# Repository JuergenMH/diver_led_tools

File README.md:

# diver_led_tools
This repository contains two projects or units.

The first one is a LED "Diver marker" and the second one is "Diver flasher".
Both devices are tools for scuba drivers.
It shares some ressources, this was the reason to put them into one repository.

## Folders
    2D drawings:            brainstorming folder with ideas how to create possible water proofed housings for the diver marker/flasher.
    documents:              different documents regarding both units.
    Firmware_diver_flasher: currently a copy of an older project which will be the base for the new software
    FIrmware_diver_marker:  ditto
    Pcb_Diver_Marker:       Eagle (7.6) PCB for this unit
    Pcb_Diver_Flasher:      KiCAD (8.0) PCB for this unit
    SKEDD-PIC-Cable:        KiCAD (8.0) schematic for the connection cable PICKIT <> PCB for program and debug purposes

## Current state (14.12.2024)
The folder structures and content are still under construction!

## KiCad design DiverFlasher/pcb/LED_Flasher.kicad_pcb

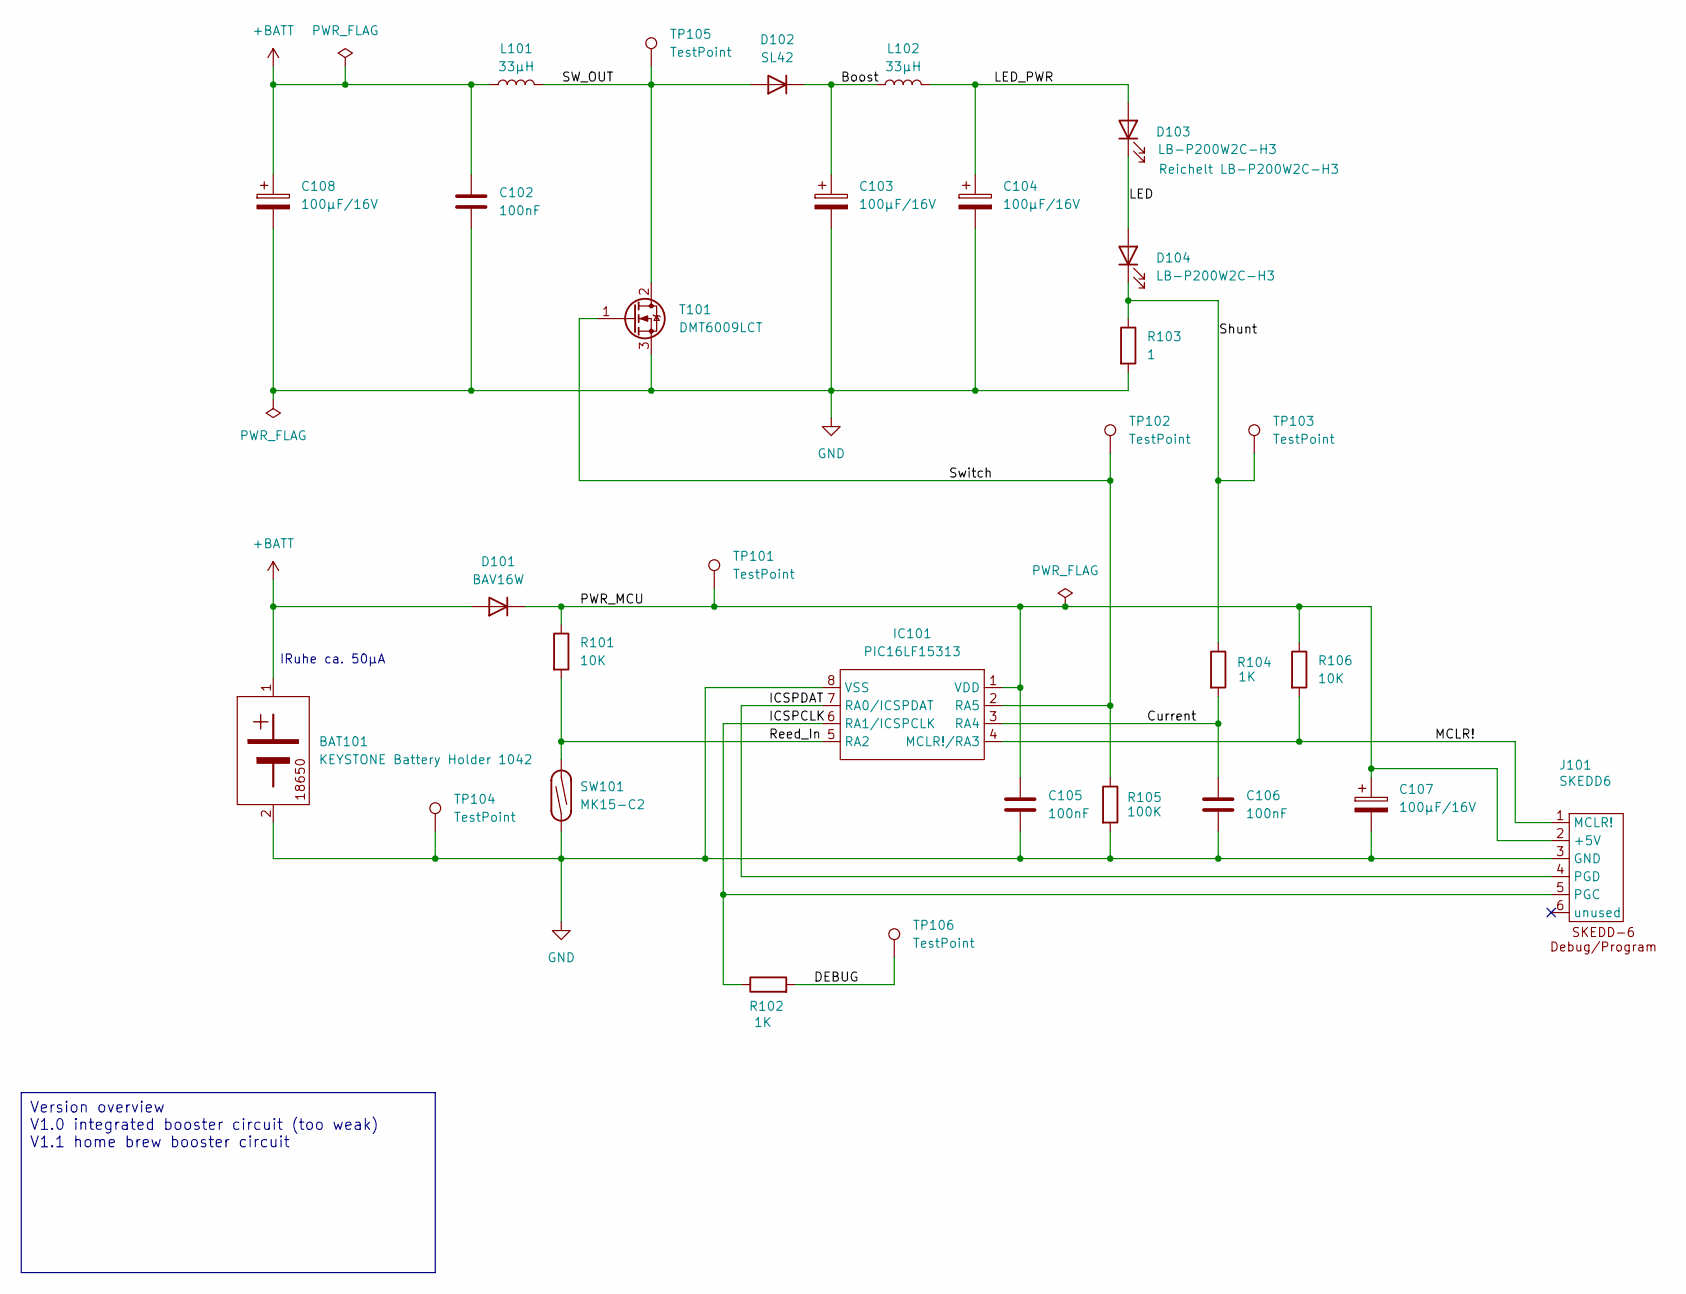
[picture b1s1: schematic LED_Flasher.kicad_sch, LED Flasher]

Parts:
BAT101: KEYSTONE Battery Holder 1042; BatteryHolder_Keystone_1042_1x18650
C102, C105, C106: 100nF; C_0805_2012Metric_Pad1.18x1.45mm_HandSolder
C103, C104, C107, C108: 100µF/16V; CP_Elec_6.3x5.8
D101: BAV16W; D_SOD-123
D102: SL42; D_SMC_Handsoldering
D103, D104: LB-P200W2C-H3; LPB200XX
IC101: PIC16LF15313; SSOP-8_3.9x5.05mm_P1.27mm
J101: SKEDD6; SKEDD-6
L101, L102: 33µH; L_12x12mm_H8mm
R101, R106: 10K; R_0805_2012Metric_Pad1.20x1.40mm_HandSolder
R102, R104: 1K; R_0805_2012Metric_Pad1.20x1.40mm_HandSolder
R103: 1; R_1206_3216Metric_Pad1.30x1.75mm_HandSolder
R105: 100K; R_0805_2012Metric_Pad1.20x1.40mm_HandSolder
SW101: MK15-C2; Meder MK15-C-2
T101: DMT6009LCT; TO-220-3_Vertical
TP101, TP102, TP103, TP104, TP105, TP106: TestPoint; TestPoint_Pad_D1.5mm

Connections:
+BATT: BAT101.1 (+), C102.1, C108.1, D101.2 (A), L101.1
/Boost: C103.1, D102.1 (K), L102.1
/Current: C106.1, IC101.3 (RA4), R104.2
/DEBUG: R102.2, TP106.1
/ICSPCLK: IC101.6 (RA1/ICSPCLK), J101.5 (PGC), R102.1
/ICSPDAT: IC101.7 (RA0/ICSPDAT), J101.4 (PGD)
/LED: D103.1 (K), D104.2 (A)
/LED_PWR: C104.1, D103.2 (A), L102.2
/MCLR!: IC101.4 (MCLR!/RA3), J101.1 (MCLR!), R106.2
/PWR_MCU: C105.1, C107.1, D101.1 (K), IC101.1 (VDD), J101.2 (+5V), R101.1, R106.1, TP101.1
/Reed_In: IC101.5 (RA2), R101.2, SW101.2
/SW_OUT: D102.2 (A), L101.2, T101.2 (D), TP105.1
/Shunt: D104.1 (K), R103.1, R104.1, TP103.1
/Switch: IC101.2 (RA5), R105.1, T101.1 (G), TP102.1
GND: BAT101.2 (-), C102.2, C103.2, C104.2, C105.2, C106.2, C107.2, C108.2, IC101.8 (VSS), J101.3 (GND), R103.2, R105.2, SW101.1, T101.3 (S), TP104.1

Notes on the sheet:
IRuhe ca. 50µA
Version overview V1.0 integrated booster circuit (too weak) V1.1 home brew booster circuit

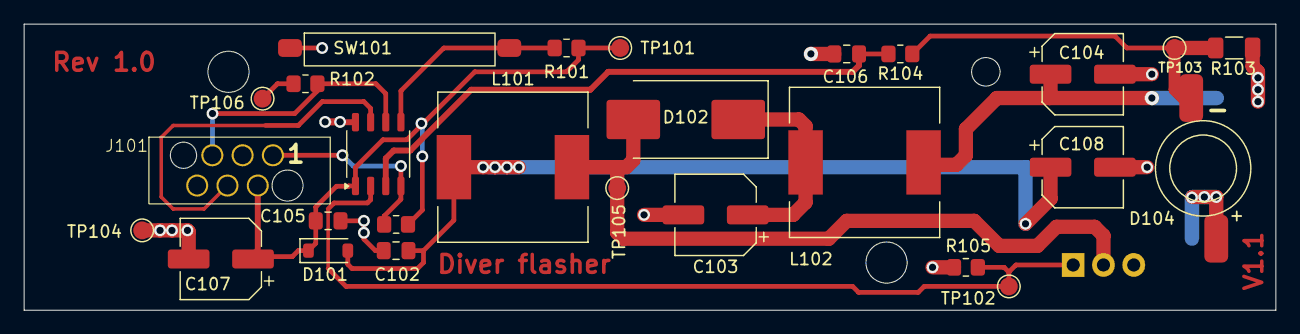
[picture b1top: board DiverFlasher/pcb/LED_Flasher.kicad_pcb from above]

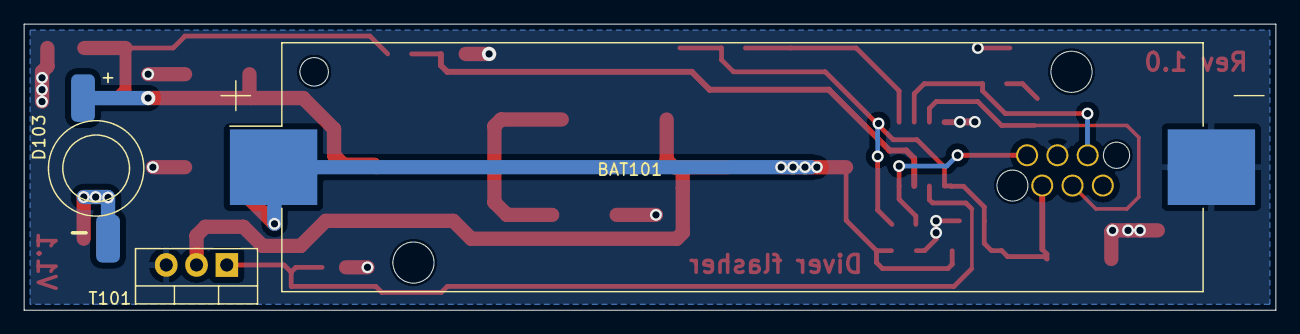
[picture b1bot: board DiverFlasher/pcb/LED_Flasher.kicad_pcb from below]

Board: 2 copper layers, 105.0 x 24.0 mm, 30 parts (3 on the bottom side), 15 nets.

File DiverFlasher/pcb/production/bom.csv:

Designator,Footprint,Quantity,Value,LCSC Part #
BAT101,BatteryHolder_Keystone_1042_1x18650,1,KEYSTONE Battery Holder 1042,
"C102, C105, C106",0805,3,100nF,
"C103, C104, C107, C108",CP_Elec_6.3x5.8,4,100µF/16V,
D101,D_SOD-123,1,BAV16W,
D102,D_SMC_Handsoldering,1,SL42,
"D103, D104",LPB200XX,2,LB-P200W2C-H3,
IC101,SSOP-8_3.9x5.05mm_P1.27mm,1,PIC16LF15313,
J101,SKEDD-6,1,SKEDD6,
"L101, L102",L_12x12mm_H8mm,2,33µH,
"R101, R106",0805,2,10K,
"R102, R104",0805,2,1K,
R103,1206,1,1,
R105,0805,1,100K,
SW101,Meder MK15-C-2,1,MK15-C2,
T101,TO-220-3_Vertical,1,DMT6009LCT,
"TP101, TP102, TP103, TP104, TP105, TP106",TestPoint_Pad_D1.5mm,6,TestPoint,

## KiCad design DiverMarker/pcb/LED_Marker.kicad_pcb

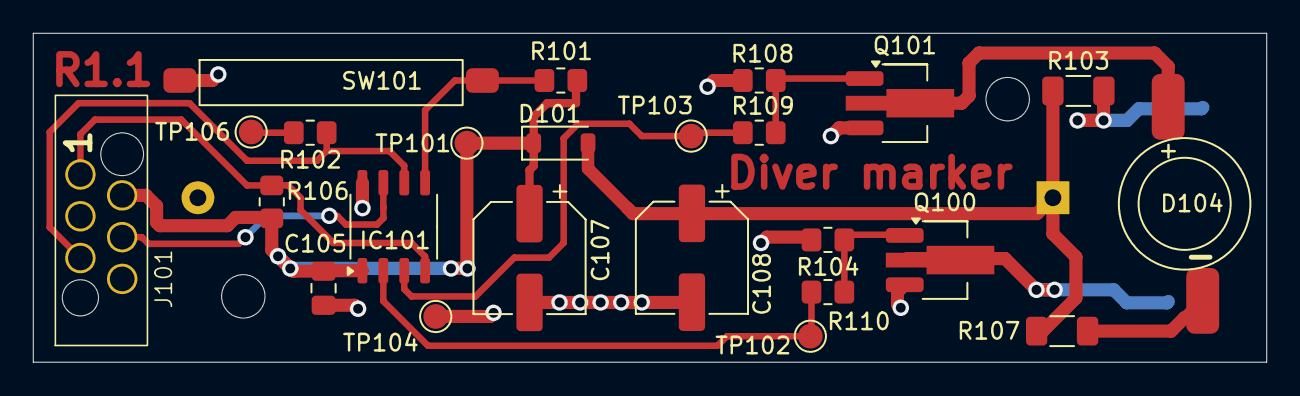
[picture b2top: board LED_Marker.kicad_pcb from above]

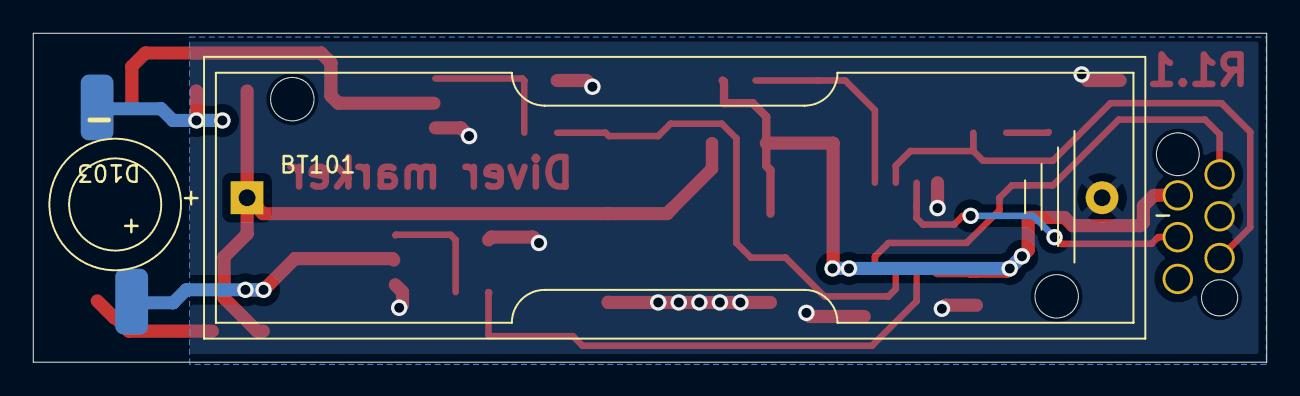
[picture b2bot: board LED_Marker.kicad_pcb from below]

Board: 2 copper layers, 75.0 x 20.0 mm, 26 parts (2 on the bottom side), 16 nets.

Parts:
BT101: Keystone 2460; BatteryHolder_Keystone_2460_1xAA
C105: 100nF; C_0805_2012Metric_Pad1.18x1.45mm_HandSolder
C107, C108: 100µF/16V; CP_Elec_6.3x5.8
D101: BAV16W; D_SOD-123
D103: LB-P200B2C-H, blue; LPB200XX
D104: LB-P200G3C-H, green; LPB200XX
IC101: PIC16LF15313; SSOP-8_3.9x5.05mm_P1.27mm
J101: SKEDD6; SKEDD-6
Q100, Q101: BST-52; SOT-89-3_Handsoldering
R101, R106: 10K; R_0805_2012Metric_Pad1.20x1.40mm_HandSolder
R102, R109, R110: 1K; R_0805_2012Metric_Pad1.20x1.40mm_HandSolder
R103, R107: 2,2; R_1206_3216Metric_Pad1.30x1.75mm_HandSolder
R104, R108: 100K; R_0805_2012Metric_Pad1.20x1.40mm_HandSolder
SW101: MK15-C2; Meder MK15-C-2
TP101, TP102, TP103, TP104, TP106: TestPoint; TestPoint_Pad_D1.5mm

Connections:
+BATT: BT101.1 (+), C108.1, D101.2 (A), R103.1, R107.1
/A_D103: D103.2 (A), R103.2
/A_D104: D104.2 (A), R107.2
/BQ100: Q100.1 (B), R104.1, R110.1
/BQ101: Q101.1 (B), R108.1, R109.1
/DEBUG: R102.2, TP106.1
/ICSPCLK: IC101.6 (RA1/ICSPCLK), J101.5 (PGC), R102.1
/ICSPDAT: IC101.7 (RA0/ICSPDAT), J101.4 (PGD)
/K_D013: D103.1 (K), Q100.2 (C)
/K_D104: D104.1 (K), Q101.2 (C)
/MCLR!: IC101.4 (MCLR!/RA3), J101.1 (MCLR!), R106.2
/PWR_MCU: C105.1, C107.1, D101.1 (K), IC101.1 (VDD), J101.2 (+5V), R101.1, R106.1, TP101.1
/Reed_In: IC101.5 (RA2), R101.2, SW101.2
BlueOn: IC101.2 (RA5), R110.2, TP102.1
GND: BT101.2 (-), C105.2, C107.2, C108.2, IC101.8 (VSS), J101.3 (GND), Q100.3 (E), Q101.3 (E), R104.2, R108.2, SW101.1, TP104.1
GreenOn: IC101.3 (RA4), R109.2, TP103.1

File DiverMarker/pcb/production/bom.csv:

Designator,Footprint,Quantity,Value,LCSC Part #
BT101,BatteryHolder_Keystone_2460_1xAA,1,Keystone 2460,
C105,0805,1,100nF,
"C107, C108",CP_Elec_6.3x5.8,2,100µF/16V,
D101,D_SOD-123,1,BAV16W,
D103,LPB200XX,1,"LB-P200B2C-H, blue",
D104,LPB200XX,1,"LB-P200G3C-H, green",
IC101,SSOP-8_3.9x5.05mm_P1.27mm,1,PIC16LF15313,
J101,SKEDD-6,1,SKEDD6,
"Q100, Q101",SOT-89-3_Handsoldering,2,BST-52,
"R101, R106",0805,2,10K,
"R102, R109, R110",0805,3,1K,
"R103, R107",1206,2,"2,2",
"R104, R108",0805,2,100K,
SW101,Meder MK15-C-2,1,MK15-C2,
"TP101, TP102, TP103, TP104, TP106",TestPoint_Pad_D1.5mm,5,TestPoint,

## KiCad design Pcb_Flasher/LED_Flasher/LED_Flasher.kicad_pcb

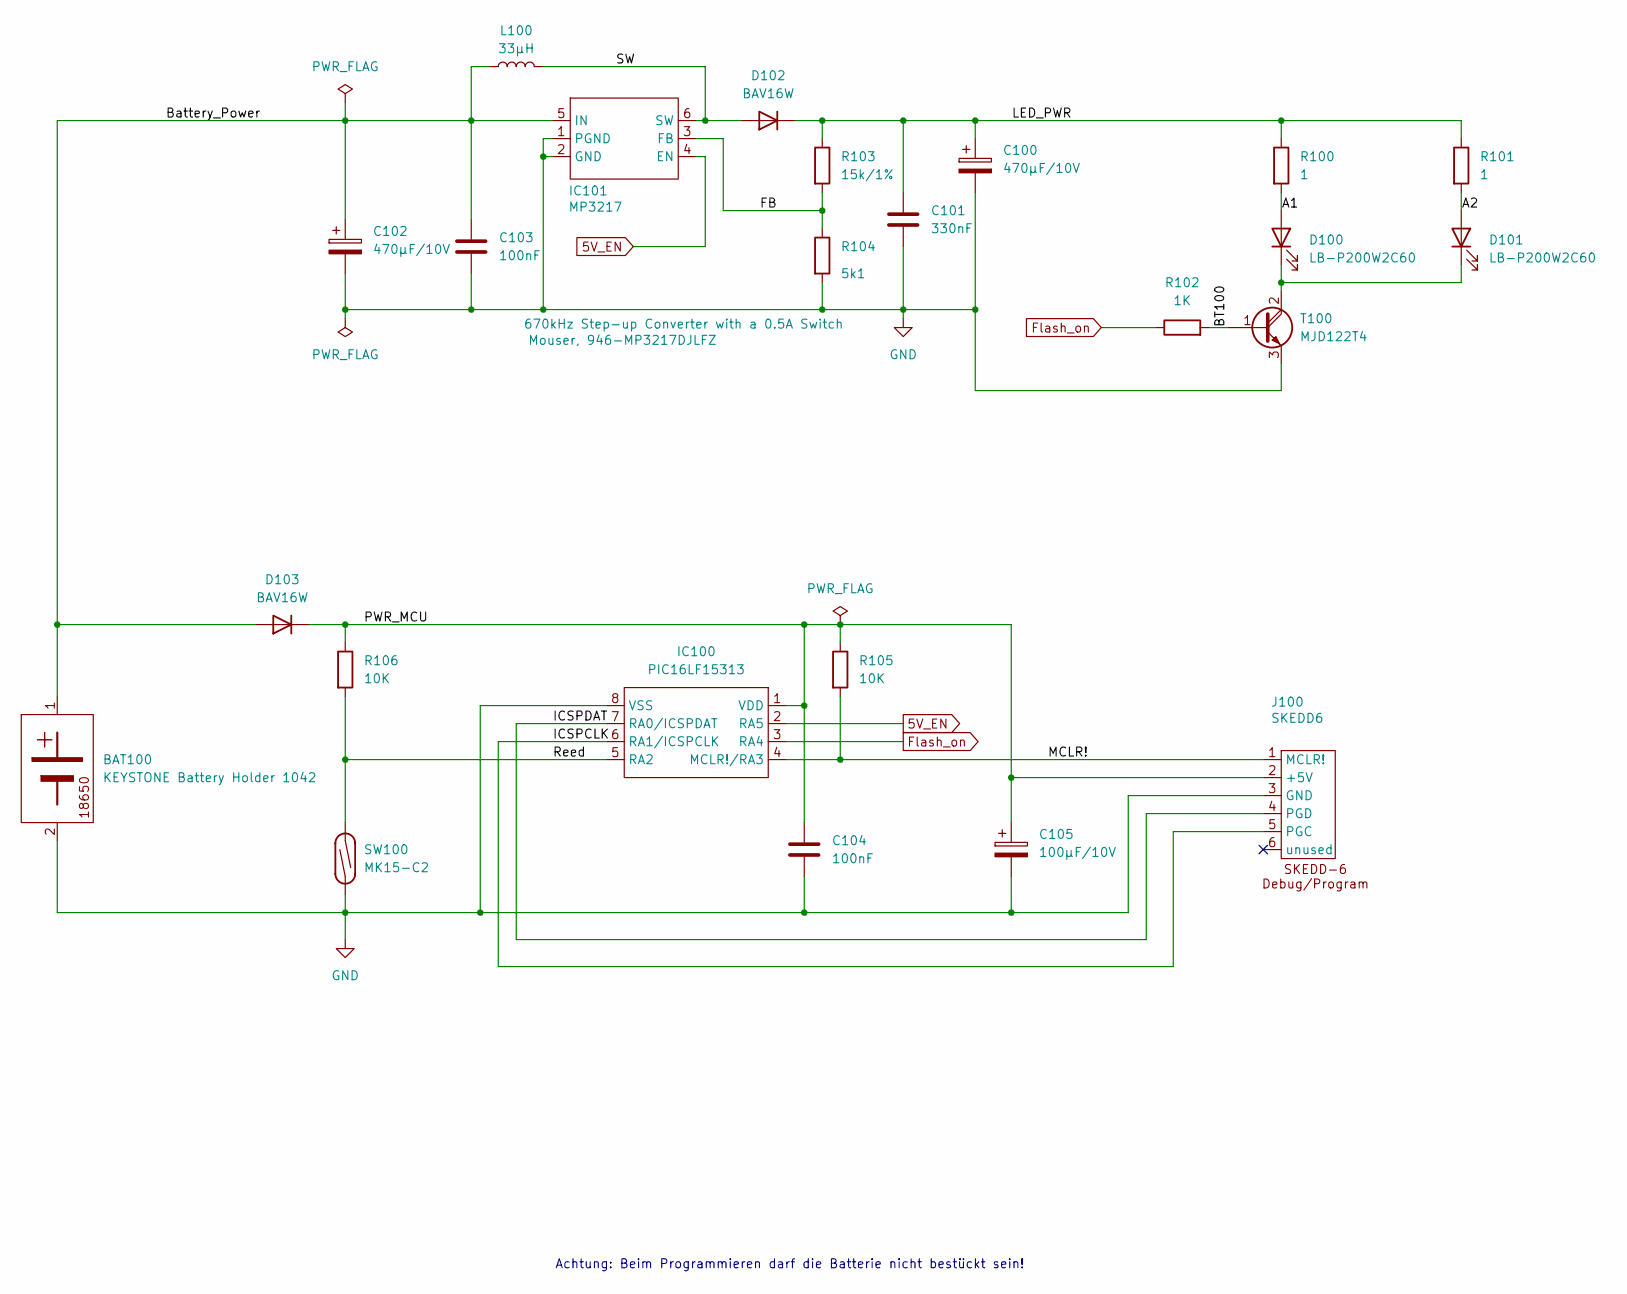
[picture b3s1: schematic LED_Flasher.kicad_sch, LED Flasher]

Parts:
BAT100: KEYSTONE Battery Holder 1042; KEYSTONE_1042
C100, C102: 470µF/10V; CP_Elec_6.3x7.7
C101: 330nF; C_0805_2012Metric_Pad1.18x1.45mm_HandSolder
C103, C104: 100nF; C_0805_2012Metric_Pad1.18x1.45mm_HandSolder
C105: 100µF/10V; CP_Elec_6.3x7.7
D100, D101: LB-P200W2C60; LPB200XX
D102, D103: BAV16W; D_SOD-123
IC100: PIC16LF15313; SSOP-8_3.9x5.05mm_P1.27mm
IC101: MP3217; TSOT-23-6
J100: SKEDD6; SKEDD-6
L100: 33µH; L_6.3x6.3_H3
R100, R101: 1; R_0805_2012Metric_Pad1.20x1.40mm_HandSolder
R102: 1K; R_0805_2012Metric_Pad1.20x1.40mm_HandSolder
R103: 15k/1%; R_0805_2012Metric_Pad1.20x1.40mm_HandSolder
R104: 5k1; R_0805_2012Metric_Pad1.20x1.40mm_HandSolder
R105, R106: 10K; R_0805_2012Metric_Pad1.20x1.40mm_HandSolder
SW100: MK15-C2; Meder MK15-C-2
T100: MJD122T4; TO-263-2

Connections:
5V_EN: IC100.2 (RA5), IC101.4 (EN)
/A1: D100.2 (A), R100.2
/A2: D101.2 (A), R101.2
/BT100: R102.2, T100.1 (B)
/Battery_Power: BAT100.1 (+), C102.1, C103.1, D103.2 (A), IC101.5 (IN), L100.1
/FB: IC101.3 (FB), R103.2, R104.1
/ICSPCLK: IC100.6 (RA1/ICSPCLK), J100.5 (PGC)
/ICSPDAT: IC100.7 (RA0/ICSPDAT), J100.4 (PGD)
/LED_PWR: C100.1, C101.1, D102.1 (K), R100.1, R101.1, R103.1
/MCLR!: IC100.4 (MCLR!/RA3), J100.1 (MCLR!), R105.2
/PWR_MCU: C104.1, C105.1, D103.1 (K), IC100.1 (VDD), J100.2 (+5V), R105.1, R106.1
/Reed: IC100.5 (RA2), R106.2, SW100.2
/SW: D102.2 (A), IC101.6 (SW), L100.2
Flash_on: IC100.3 (RA4), R102.1
GND: BAT100.2 (-), C100.2, C101.2, C102.2, C103.2, C104.2, C105.2, IC100.8 (VSS), IC101.1 (PGND), IC101.2 (GND), J100.3 (GND), R104.2, SW100.1, T100.3 (E)
unnamed: D100.1 (K), D101.1 (K), T100.2 (C)

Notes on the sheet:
Achtung: Beim Programmieren darf die Batterie nicht bestückt sein!

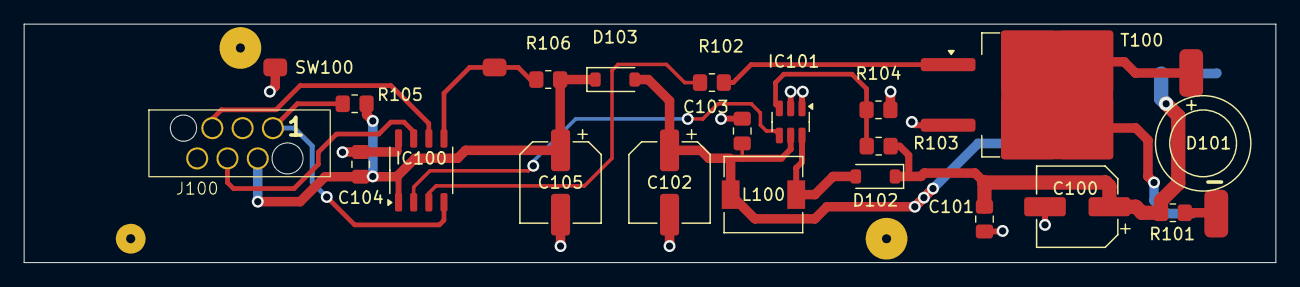
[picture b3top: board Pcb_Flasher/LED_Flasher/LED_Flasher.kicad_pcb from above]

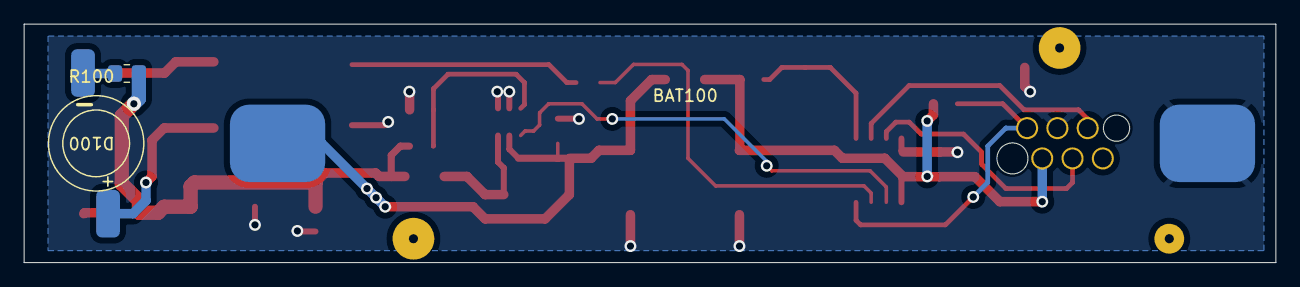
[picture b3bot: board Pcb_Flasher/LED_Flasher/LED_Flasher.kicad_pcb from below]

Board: 2 copper layers, 105.0 x 20.0 mm, 24 parts (3 on the bottom side), 16 nets.

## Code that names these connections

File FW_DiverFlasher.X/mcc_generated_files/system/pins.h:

/**
 * Generated Pins header File
 * 
 * @file pins.h
 * 
 * @defgroup  pinsdriver Pins Driver
 * 
 * @brief This is generated driver header for pins. 
 *        This header file provides APIs for all pins selected in the GUI.
 *
 * @version Driver Version  3.0.0
*/

/*
© [2025] Microchip Technology Inc. and its subsidiaries.

    Subject to your compliance with these terms, you may use Microchip 
    software and any derivatives exclusively with Microchip products. 
    You are responsible for complying with 3rd party license terms  
    applicable to your use of 3rd party software (including open source  
    software) that may accompany Microchip software. SOFTWARE IS ?AS IS.? 
    NO WARRANTIES, WHETHER EXPRESS, IMPLIED OR STATUTORY, APPLY TO THIS 
    SOFTWARE, INCLUDING ANY IMPLIED WARRANTIES OF NON-INFRINGEMENT,  
    MERCHANTABILITY, OR FITNESS FOR A PARTICULAR PURPOSE. IN NO EVENT 
    WILL MICROCHIP BE LIABLE FOR ANY INDIRECT, SPECIAL, PUNITIVE, 
    INCIDENTAL OR CONSEQUENTIAL LOSS, DAMAGE, COST OR EXPENSE OF ANY 
    KIND WHATSOEVER RELATED TO THE SOFTWARE, HOWEVER CAUSED, EVEN IF 
    MICROCHIP HAS BEEN ADVISED OF THE POSSIBILITY OR THE DAMAGES ARE 
    FORESEEABLE. TO THE FULLEST EXTENT ALLOWED BY LAW, MICROCHIP?S 
    TOTAL LIABILITY ON ALL CLAIMS RELATED TO THE SOFTWARE WILL NOT 
    EXCEED AMOUNT OF FEES, IF ANY, YOU PAID DIRECTLY TO MICROCHIP FOR 
    THIS SOFTWARE.
*/

#ifndef PINS_H
#define PINS_H

#include <xc.h>

#define INPUT   1
#define OUTPUT  0

#define HIGH    1
#define LOW     0

#define ANALOG      1
#define DIGITAL     0

#define PULL_UP_ENABLED      1
#define PULL_UP_DISABLED     0

// get/set IO_RA0 aliases
#define IO_RA0_TRIS                 TRISAbits.TRISA0
#define IO_RA0_LAT                  LATAbits.LATA0
#define IO_RA0_PORT                 PORTAbits.RA0
#define IO_RA0_WPU                  WPUAbits.WPUA0
#define IO_RA0_OD                   ODCONAbits.ODCA0
#define IO_RA0_ANS                  ANSELAbits.ANSA0
#define IO_RA0_SetHigh()            do { LATAbits.LATA0 = 1; } while(0)
#define IO_RA0_SetLow()             do { LATAbits.LATA0 = 0; } while(0)
#define IO_RA0_Toggle()             do { LATAbits.LATA0 = ~LATAbits.LATA0; } while(0)
#define IO_RA0_GetValue()           PORTAbits.RA0
#define IO_RA0_SetDigitalInput()    do { TRISAbits.TRISA0 = 1; } while(0)
#define IO_RA0_SetDigitalOutput()   do { TRISAbits.TRISA0 = 0; } while(0)
#define IO_RA0_SetPullup()          do { WPUAbits.WPUA0 = 1; } while(0)
#define IO_RA0_ResetPullup()        do { WPUAbits.WPUA0 = 0; } while(0)
#define IO_RA0_SetPushPull()        do { ODCONAbits.ODCA0 = 0; } while(0)
#define IO_RA0_SetOpenDrain()       do { ODCONAbits.ODCA0 = 1; } while(0)
#define IO_RA0_SetAnalogMode()      do { ANSELAbits.ANSA0 = 1; } while(0)
#define IO_RA0_SetDigitalMode()     do { ANSELAbits.ANSA0 = 0; } while(0)
// get/set IO_RA1 aliases
#define Debug_TRIS                 TRISAbits.TRISA1
#define Debug_LAT                  LATAbits.LATA1
#define Debug_PORT                 PORTAbits.RA1
#define Debug_WPU                  WPUAbits.WPUA1
#define Debug_OD                   ODCONAbits.ODCA1
#define Debug_ANS                  ANSELAbits.ANSA1
#define Debug_SetHigh()            do { LATAbits.LATA1 = 1; } while(0)
#define Debug_SetLow()             do { LATAbits.LATA1 = 0; } while(0)
#define Debug_Toggle()             do { LATAbits.LATA1 = ~LATAbits.LATA1; } while(0)
#define Debug_GetValue()           PORTAbits.RA1
#define Debug_SetDigitalInput()    do { TRISAbits.TRISA1 = 1; } while(0)
#define Debug_SetDigitalOutput()   do { TRISAbits.TRISA1 = 0; } while(0)
#define Debug_SetPullup()          do { WPUAbits.WPUA1 = 1; } while(0)
#define Debug_ResetPullup()        do { WPUAbits.WPUA1 = 0; } while(0)
#define Debug_SetPushPull()        do { ODCONAbits.ODCA1 = 0; } while(0)
#define Debug_SetOpenDrain()       do { ODCONAbits.ODCA1 = 1; } while(0)
#define Debug_SetAnalogMode()      do { ANSELAbits.ANSA1 = 1; } while(0)
#define Debug_SetDigitalMode()     do { ANSELAbits.ANSA1 = 0; } while(0)
// get/set IO_RA2 aliases
#define Reed_TRIS                 TRISAbits.TRISA2
#define Reed_LAT                  LATAbits.LATA2
#define Reed_PORT                 PORTAbits.RA2
#define Reed_WPU                  WPUAbits.WPUA2
#define Reed_OD                   ODCONAbits.ODCA2
#define Reed_ANS                  ANSELAbits.ANSA2
#define Reed_SetHigh()            do { LATAbits.LATA2 = 1; } while(0)
#define Reed_SetLow()             do { LATAbits.LATA2 = 0; } while(0)
#define Reed_Toggle()             do { LATAbits.LATA2 = ~LATAbits.LATA2; } while(0)
#define Reed_GetValue()           PORTAbits.RA2
#define Reed_SetDigitalInput()    do { TRISAbits.TRISA2 = 1; } while(0)
#define Reed_SetDigitalOutput()   do { TRISAbits.TRISA2 = 0; } while(0)
#define Reed_SetPullup()          do { WPUAbits.WPUA2 = 1; } while(0)
#define Reed_ResetPullup()        do { WPUAbits.WPUA2 = 0; } while(0)
#define Reed_SetPushPull()        do { ODCONAbits.ODCA2 = 0; } while(0)
#define Reed_SetOpenDrain()       do { ODCONAbits.ODCA2 = 1; } while(0)
#define Reed_SetAnalogMode()      do { ANSELAbits.ANSA2 = 1; } while(0)
#define Reed_SetDigitalMode()     do { ANSELAbits.ANSA2 = 0; } while(0)
// get/set IO_RA4 aliases
#define Current_TRIS                 TRISAbits.TRISA4
#define Current_LAT                  LATAbits.LATA4
#define Current_PORT                 PORTAbits.RA4
#define Current_WPU                  WPUAbits.WPUA4
#define Current_OD                   ODCONAbits.ODCA4
#define Current_ANS                  ANSELAbits.ANSA4
#define Current_SetHigh()            do { LATAbits.LATA4 = 1; } while(0)
#define Current_SetLow()             do { LATAbits.LATA4 = 0; } while(0)
#define Current_Toggle()             do { LATAbits.LATA4 = ~LATAbits.LATA4; } while(0)
#define Current_GetValue()           PORTAbits.RA4
#define Current_SetDigitalInput()    do { TRISAbits.TRISA4 = 1; } while(0)
#define Current_SetDigitalOutput()   do { TRISAbits.TRISA4 = 0; } while(0)
#define Current_SetPullup()          do { WPUAbits.WPUA4 = 1; } while(0)
#define Current_ResetPullup()        do { WPUAbits.WPUA4 = 0; } while(0)
#define Current_SetPushPull()        do { ODCONAbits.ODCA4 = 0; } while(0)
#define Current_SetOpenDrain()       do { ODCONAbits.ODCA4 = 1; } while(0)
#define Current_SetAnalogMode()      do { ANSELAbits.ANSA4 = 1; } while(0)
#define Current_SetDigitalMode()     do { ANSELAbits.ANSA4 = 0; } while(0)
// get/set IO_RA5 aliases
#define Switch_TRIS                 TRISAbits.TRISA5
#define Switch_LAT                  LATAbits.LATA5
#define Switch_PORT                 PORTAbits.RA5
#define Switch_WPU                  WPUAbits.WPUA5
#define Switch_OD                   ODCONAbits.ODCA5
#define Switch_ANS                  ANSELAbits.ANSA5
#define Switch_SetHigh()            do { LATAbits.LATA5 = 1; } while(0)
#define Switch_SetLow()             do { LATAbits.LATA5 = 0; } while(0)
#define Switch_Toggle()             do { LATAbits.LATA5 = ~LATAbits.LATA5; } while(0)
#define Switch_GetValue()           PORTAbits.RA5
#define Switch_SetDigitalInput()    do { TRISAbits.TRISA5 = 1; } while(0)
#define Switch_SetDigitalOutput()   do { TRISAbits.TRISA5 = 0; } while(0)
#define Switch_SetPullup()          do { WPUAbits.WPUA5 = 1; } while(0)
#define Switch_ResetPullup()        do { WPUAbits.WPUA5 = 0; } while(0)
#define Switch_SetPushPull()        do { ODCONAbits.ODCA5 = 0; } while(0)
#define Switch_SetOpenDrain()       do { ODCONAbits.ODCA5 = 1; } while(0)
#define Switch_SetAnalogMode()      do { ANSELAbits.ANSA5 = 1; } while(0)
#define Switch_SetDigitalMode()     do { ANSELAbits.ANSA5 = 0; } while(0)
/**
 * @ingroup  pinsdriver
 * @brief GPIO and peripheral I/O initialization
 * @param none
 * @return none
 */
void PIN_MANAGER_Initialize (void);

/**
 * @ingroup  pinsdriver
 * @brief Interrupt on Change Handling routine
 * @param none
 * @return none
 */
void PIN_MANAGER_IOC(void);


#endif // PINS_H
/**
 End of File
*/

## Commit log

2024-12-14 Initial commit to add existing files and folders to the empty repository
2024-12-14 Update README.md
    Readme changed for test purposes only.
2024-12-16 SW adapted for new hardware
    First version for new hardware, can be compiled but it is not tested yet.
2024-12-18 Inter mediate check in
    HW: is working; LED current propably to low
    SW: Basic functions are working.
    System enters sleep; wakeup not working
    Switch handling for manual on/off not implemented
2024-12-18 Sleep / Wakeup now working
    Auto power off still set to one minute (for easy debugging)
    Next todo: Implement user power off
2024-12-18 First working version of the software
    Reed switch handling implemented
    - Reed activated = flasher running
    - Reed deactivated = flasher enter sleep
    If flasher is activated for 90 minutes it will enter auto power off.
2024-12-26 Information regaring inductor and diode added
2024-12-26 Document with issues first prototype added. Word / German
2024-12-26 Intermediate check in
2025-01-03 Simulation folder added
    A simulation for a more powerful booster circuit was added.
2025-01-06 New datasheets and simulations added. Target is to improve the power of the booster circuit of the diver flasher.
2025-01-12 backups removed
2025-01-12 ignore fie added.
2025-01-15 again; zip files removed
2025-01-15 Started with version 1.1 of the dive flasher PCB. 1.0 => old too weak booster 1.1 => new hopefully more powerful booster
2025-02-09 New simulation added.
2025-02-09 Start with next version "home brew" boost converter
2025-02-19 Firmware folder diver flasher renamed Software new generated with melody framework
2025-02-21 New FW structure added for diver marker No functions implemented yet
2025-02-21 New structure for the diver marker. Ready: Pulse generation Tested on desk only: basic I regulation of pulse width Application: 50ms on, 950ms off, not power up/down yet
2025-02-21 PCB diver flasher restored
2025-03-03 Update to KiCAD 9
2025-03-03 main.c is working now
2025-03-09 Old PC (v1) removed Latest changes for current schematic routed. Almost ready DRC outstanding.
2025-03-09 Project reorganised: - Outdate and backup files removed - diver flasher and diver marker moved to separate folders
2025-03-28 New pcb design with KiCAD 9 started. Old eagle design moved to archive folder.
2025-04-04 DRC errors removed, finished
2025-04-07 Backup files removed
2025-04-09 Routing PCB diver marker started; almost ready but a least of open drc errors.
2025-04-09 pcb finished errors almost removed
2025-04-10 Unused datasheets removed Keystone 1024 tested but not used because of space requirements. Still THT version used on board.
2025-04-10 Updates on Backup folder
2025-04-11 Two additional inductor types from Würth added.
2025-04-11 Distributors for all componentes added.
2025-04-12 Working on BON
2025-04-14 Working on PCB documentation
2025-04-27 Component placement optimisation. No functional changes
2025-04-27 PCB sizes added on layer user 1
2025-04-27 Production data with JLCPCB plugin generated
2025-05-04 Side view of the PCB on measurement layer added.
2025-05-04 Side View on Measurment layer added
2025-05-07 No functional changes
2025-05-07 Setup firmware within MCC, coding startet; timer not running correct yet.
2025-05-07 PCB informations added
2025-05-09 Work on firmware / HW - activate sleep (not finished yet) - To Do list for next version PCB added
2025-05-09 Work on HW and SW
    - To Do list for next version of pcb
    - Start coding firmware (currently issue with PA.5)
2025-05-09 PortA.5 issue fixed (External oszillator was not disabled; Clock setup)
2025-05-09 Working on sleep mode Currently no wakeup
2025-05-10 Sleep and wakeup are working now. On time is minimum 3 cycles.
    ToDo: Check current consumption to validate HW and SW for battery life time.
2025-05-10 Sleep and wakeup is working now. Minimum on cycles is 3 cycles
    => at this moment same user logic as diver flasher!
    Next steps:
    - Implement 2 or 3 different lightning levels (SW)
    - Validate current consumption to validate HW and SW
2025-05-10 Ruhestrom hinzugefügt (50µA)
2025-05-10 Änderung durch MPLab
2025-05-10 Minor changes: - LED blue replaced by red one (curret is on blue too low) - LED resistors changed from 2.2Ohm to 1Ohm - quiescent current added (about 25µA)
2025-05-10 Two power modes added.
    Cycle on, off, on agwain within the first min cycle switches to high power
2025-05-11 Intensity method changed from time (not good) to a software PWM (much better).
2025-05-12 Timing und current check. No functional changes
2025-05-18 Platineneigenschaften und Lagenaufbau au PCB-Sheet hinzugefügt.
2025-05-18 Materialrecherche Amazon hinzugefügt.
2025-05-24 Weitere Daten zu Gehäuseinformationen hinzugefügt
2025-05-24 Global .ignore file added Empty folders with dummy content to get structure into repo.
2025-05-24 Local .gitignore by project global replaced.
2025-05-24 production zip added
2025-05-24 Document folder added.
2025-05-24 - Archiv removed - Document folder added
2025-05-24 Battery calculation update
2025-05-31 Drawing of bottom housing part added.
2025-05-31 Two more accu datasheets.
2025-05-31 Rohrbodenzeichnung vervollständigt.
2025-06-28 Datasheet update
2025-06-28 Calculation update regarding last measurements
2025-06-28 Table with current measurements added.
2025-06-30 Mechanical BOM added
2025-07-07 Adjusted CPU frequency from 32MHz to 1Mhz.
